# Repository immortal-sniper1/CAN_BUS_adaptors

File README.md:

# CAN_BUS_adaptors
 A few boards that bridge CAN bus to SPI/serial.
 The shields are compatible with:     
  Arduino UNO (or compatible form factor)        
    ESP32 devkitC        
    STM32 NUCLEO-64/144 boards.

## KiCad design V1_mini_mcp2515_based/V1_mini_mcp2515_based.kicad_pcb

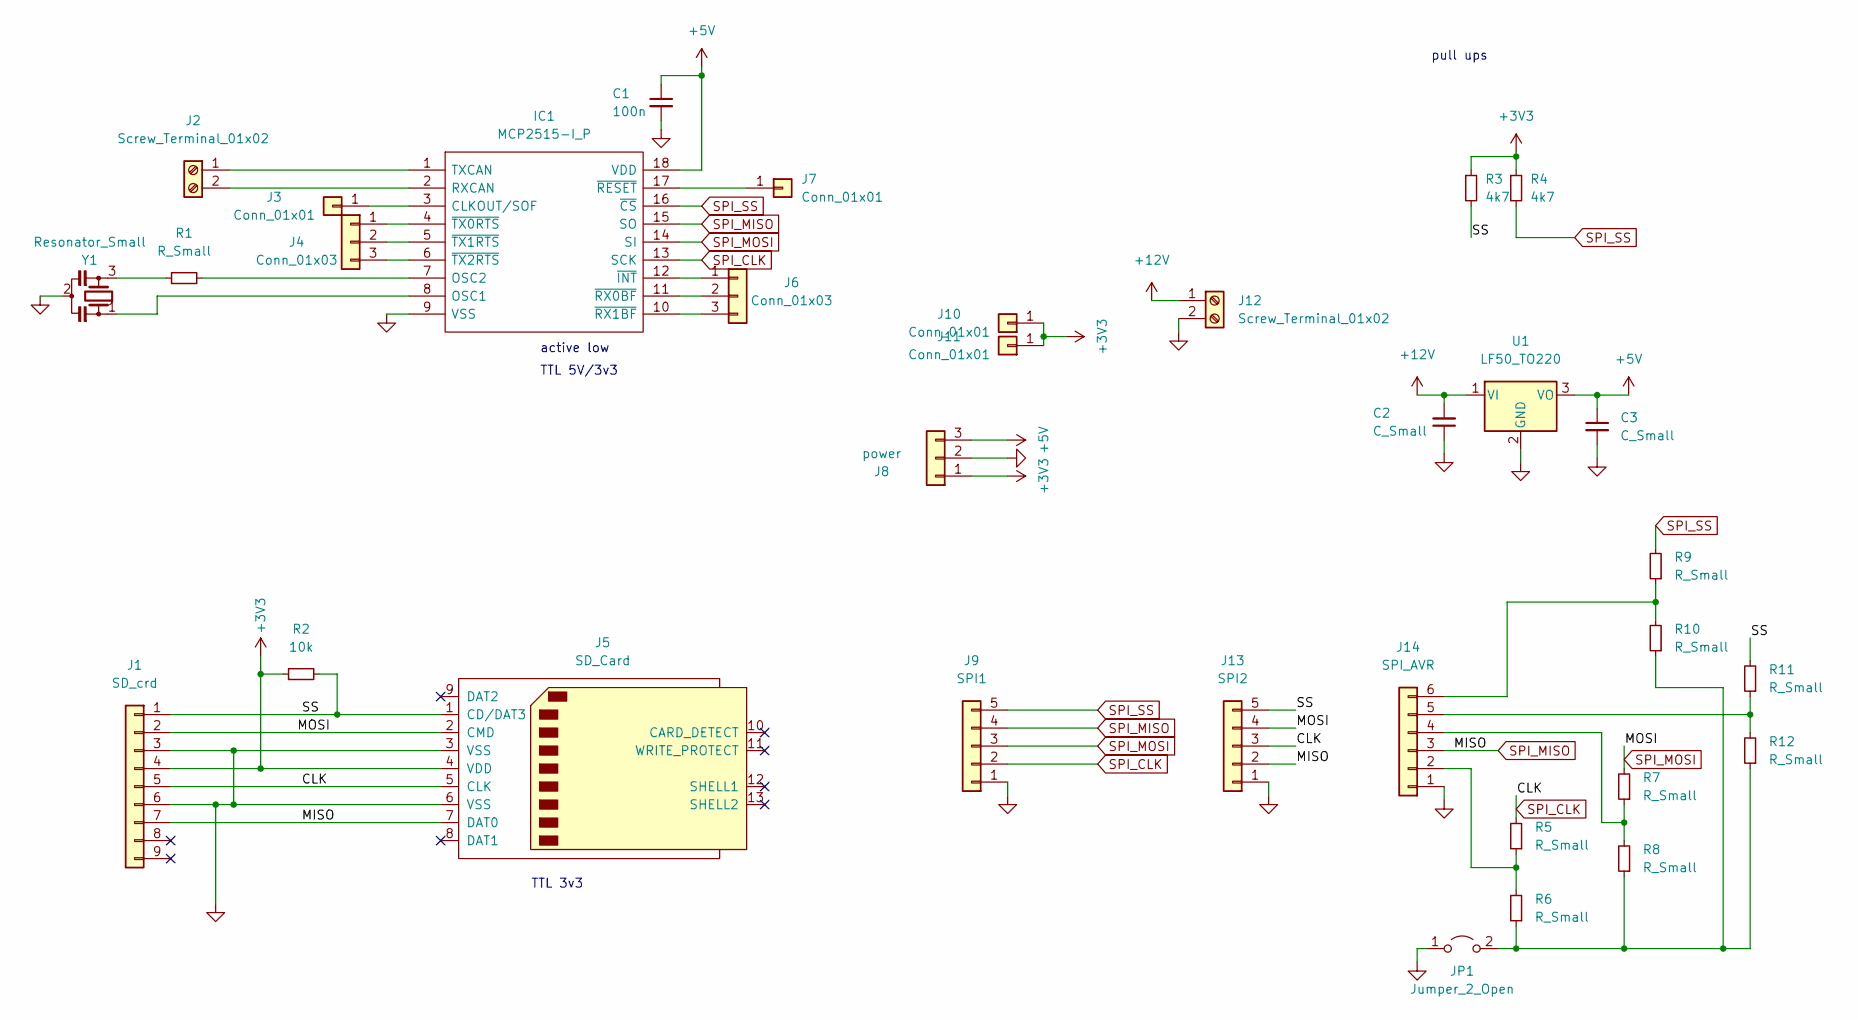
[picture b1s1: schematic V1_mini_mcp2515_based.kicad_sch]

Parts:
C1: 100n; C_Disc_D4.7mm_W2.5mm_P5.00mm
C2, C3: C_Small; C_Disc_D4.3mm_W1.9mm_P5.00mm
IC1: MCP2515-I_P; DIP-18_W7.62mm_LongPads; Mouser Part Number 579-MCP2515-I/P
J1: SD_crd; PinHeader_1x07_P2.54mm_Vertical
J2, J12: Screw_Terminal_01x02; TerminalBlock_Altech_AK300-2_P5.00mm
J3, J7, J10, J11: Conn_01x01; PinHeader_1x01_P2.54mm_Vertical
J4, J6: Conn_01x03; PinHeader_1x03_P2.54mm_Vertical
J5: SD_Card
J8: power; PinHeader_1x03_P2.54mm_Vertical
J9: SPI1; PinHeader_1x05_P2.54mm_Vertical
J13: SPI2; PinHeader_1x05_P2.54mm_Vertical
J14: SPI_AVR; PinHeader_1x06_P2.54mm_Vertical
JP1: Jumper_2_Open; PinHeader_1x02_P2.54mm_Vertical
R1, R5, R6, R7, R8, R9, R10, R11, R12: R_Small; R_Axial_DIN0204_L3.6mm_D1.6mm_P5.08mm_Horizontal
R2: 10k; R_Axial_DIN0204_L3.6mm_D1.6mm_P5.08mm_Horizontal
R3, R4: 4k7; R_Axial_DIN0204_L3.6mm_D1.6mm_P5.08mm_Horizontal
U1: LF50_TO220; TO-220-3_Horizontal_TabDown
Y1: Resonator_Small; Resonator_Murata_CSTLSxxxG-3Pin_W8.0mm_H3.0mm

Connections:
+3V3: J1.4, J5.4 (VDD), J8.1, J10.1, J11.1, R2.1, R3.1, R4.1
+5V: C1.1, C3.1, IC1.18 (VDD), J8.3, U1.3 (VO)
+12V: C2.2, J12.1, U1.1 (VI)
/SS: J1.1, J5.1 (CD/DAT3), J13.5, R2.2, R3.2, R11.2
GND: C1.2, C2.1, C3.2, IC1.9 (VSS), J1.3, J1.6, J5.3 (VSS), J5.6 (VSS), J8.2, J9.1, J12.2, J13.1, J14.1, JP1.1 (A), U1.2 (GND), Y1.2
unnamed: IC1.1 (TXCAN), J2.1
unnamed: IC1.2 (RXCAN), J2.2
unnamed: IC1.3 (CLKOUT/SOF), J3.1
unnamed: IC1.4 (~TX0RTS), J4.1
unnamed: IC1.5 (~TX1RTS), J4.2
unnamed: IC1.6 (~TX2RTS), J4.3
unnamed: IC1.7 (OSC2), R1.2
unnamed: IC1.8 (OSC1), Y1.1
unnamed: IC1.10 (~RX1BF), J6.3
unnamed: IC1.11 (~RX0BF), J6.2
unnamed: IC1.12 (~INT), J6.1
unnamed: IC1.17 (~RESET), J7.1
unnamed: J14.2, R5.1, R6.2
unnamed: J14.4, R7.1, R8.2
unnamed: J14.5, R11.1, R12.2
unnamed: J14.6, R9.1, R10.2
unnamed: JP1.2 (B), R6.1, R8.1, R10.1, R12.1
unnamed: R1.1, Y1.3
SPI_CLK: IC1.13 (SCK), J1.5, J5.5 (CLK), J9.2, J13.3, R5.2
SPI_MISO: IC1.15 (SO), J1.7, J5.7 (DAT0), J9.4, J13.2, J14.3
SPI_MOSI: IC1.14 (SI), J1.2, J5.2 (CMD), J9.3, J13.4, R7.2
SPI_SS: IC1.16 (~CS), J9.5, R4.2, R9.2

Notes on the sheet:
TTL 5V/3v3
active low
pull ups
TTL 3v3

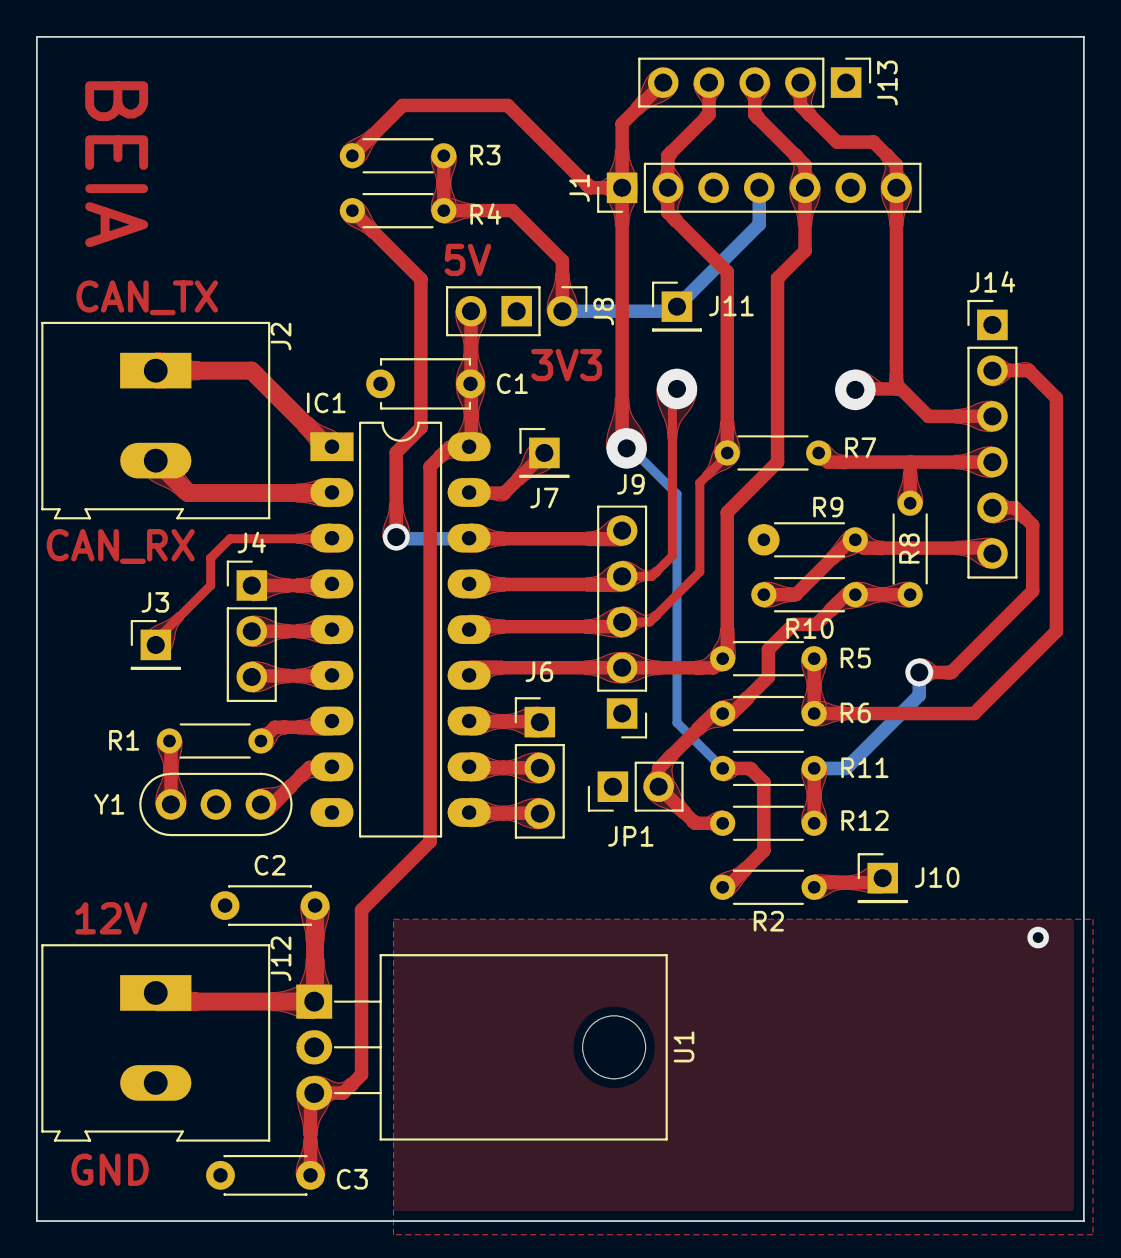
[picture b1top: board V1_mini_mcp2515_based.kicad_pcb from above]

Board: 2 copper layers, 58.2 x 65.8 mm, 32 parts (0 on the bottom side), 27 nets.

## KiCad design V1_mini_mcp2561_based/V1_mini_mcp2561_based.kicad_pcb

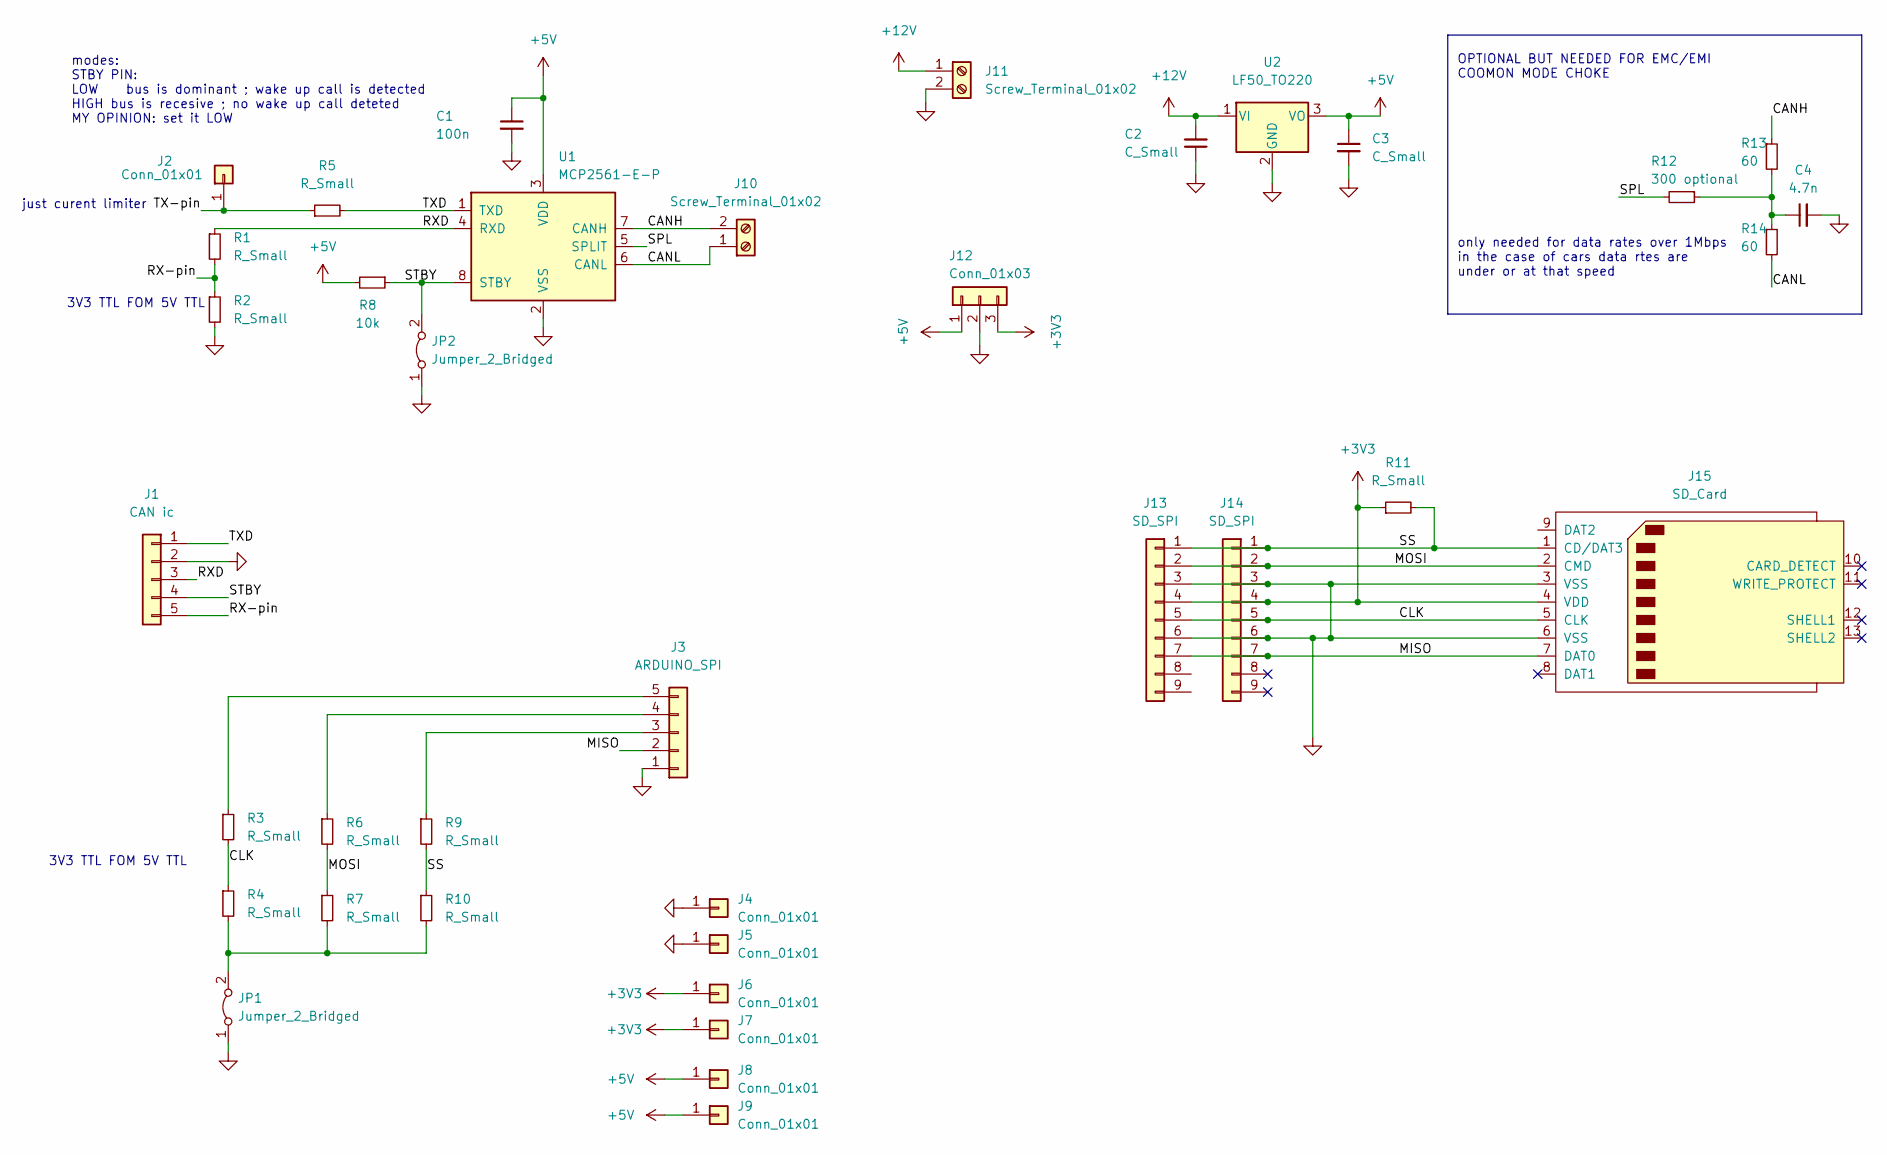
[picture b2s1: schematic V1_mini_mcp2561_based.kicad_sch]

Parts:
C1: 100n; C_Disc_D4.3mm_W1.9mm_P5.00mm
C2: C_Small; CP_Radial_Tantal_D5.0mm_P5.00mm
C3: C_Small; C_Disc_D4.3mm_W1.9mm_P5.00mm
C4: 4.7n; C_Disc_D4.3mm_W1.9mm_P5.00mm
J1: CAN ic; PinHeader_1x05_P2.54mm_Vertical
J2, J4, J5, J6, J7, J8, J9: Conn_01x01; PinHeader_1x01_P2.54mm_Vertical
J3: ARDUINO_SPI; PinHeader_1x05_P2.54mm_Vertical
J10, J11: Screw_Terminal_01x02; TerminalBlock_Altech_AK300-2_P5.00mm
J12: Conn_01x03; PinHeader_1x03_P2.54mm_Vertical
J13, J14: SD_SPI; PinHeader_1x07_P2.54mm_Vertical
J15: SD_Card
JP1, JP2: Jumper_2_Bridged; PinHeader_1x02_P2.54mm_Vertical
R1, R2, R3, R4, R5, R6, R7, R9, R10, R11: R_Small; R_Axial_DIN0204_L3.6mm_D1.6mm_P5.08mm_Horizontal
R8: 10k; R_Axial_DIN0204_L3.6mm_D1.6mm_P5.08mm_Horizontal
R12: 300 optional; R_Axial_DIN0204_L3.6mm_D1.6mm_P5.08mm_Horizontal
R13, R14: 60; R_Axial_DIN0204_L3.6mm_D1.6mm_P5.08mm_Horizontal
U1: MCP2561-E-P; DIP-8_W7.62mm_LongPads
U2: LF50_TO220; TO-220-3_Horizontal_TabDown

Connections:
+3V3: J6.1, J7.1, J12.3, J13.4, J14.4, J15.4 (VDD), R11.1
+5V: C1.1, C3.1, J8.1, J9.1, J12.1, R8.2, U1.3 (VDD), U2.3 (VO)
+12V: C2.2, J11.1, U2.1 (VI)
/CANH: J10.2, R13.1, U1.7 (CANH)
/CANL: J10.1, R14.2, U1.6 (CANL)
/CLK: J13.5, J14.5, J15.5 (CLK), R3.2, R4.1
/MISO: J3.2, J13.7, J14.7, J15.7 (DAT0)
/MOSI: J13.2, J14.2, J15.2 (CMD), R6.2, R7.1
/RX-pin: J1.5, R1.2, R2.1
/RXD: J1.3, R1.1, U1.4 (RXD)
/SPL: R12.2, U1.5 (SPLIT)
/SS: J13.1, J14.1, J15.1 (CD/DAT3), R9.2, R10.1, R11.2
/STBY: J1.4, JP2.2 (B), R8.1, U1.8 (STBY)
/TX-pin: J2.1, R5.1
/TXD: J1.1, R5.2, U1.1 (TXD)
GND: C1.2, C2.1, C3.2, C4.2, J1.2, J3.1, J4.1, J5.1, J11.2, J12.2, J13.3, J13.6, J14.3, J14.6, J15.3 (VSS), J15.6 (VSS), JP1.1 (A), JP2.1 (A), R2.2, U1.2 (VSS), U2.2 (GND)
unnamed: C4.1, R12.1, R13.2, R14.1
unnamed: J3.3, R9.1
unnamed: J3.4, R6.1
unnamed: J3.5, R3.1
unnamed: JP1.2 (B), R4.2, R7.2, R10.2

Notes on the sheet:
3V3 TTL FOM 5V TTL
only needed for data rates over 1Mbps in the case of cars data rtes are under or at that speed
OPTIONAL BUT NEEDED FOR EMC/EMI COOMON MODE CHOKE
modes: STBY PIN: LOW bus is dominant ; wake up call is detected HIGH bus is recesive ; no wake up call deteted MY OPINION: set it LOW
just curent limiter

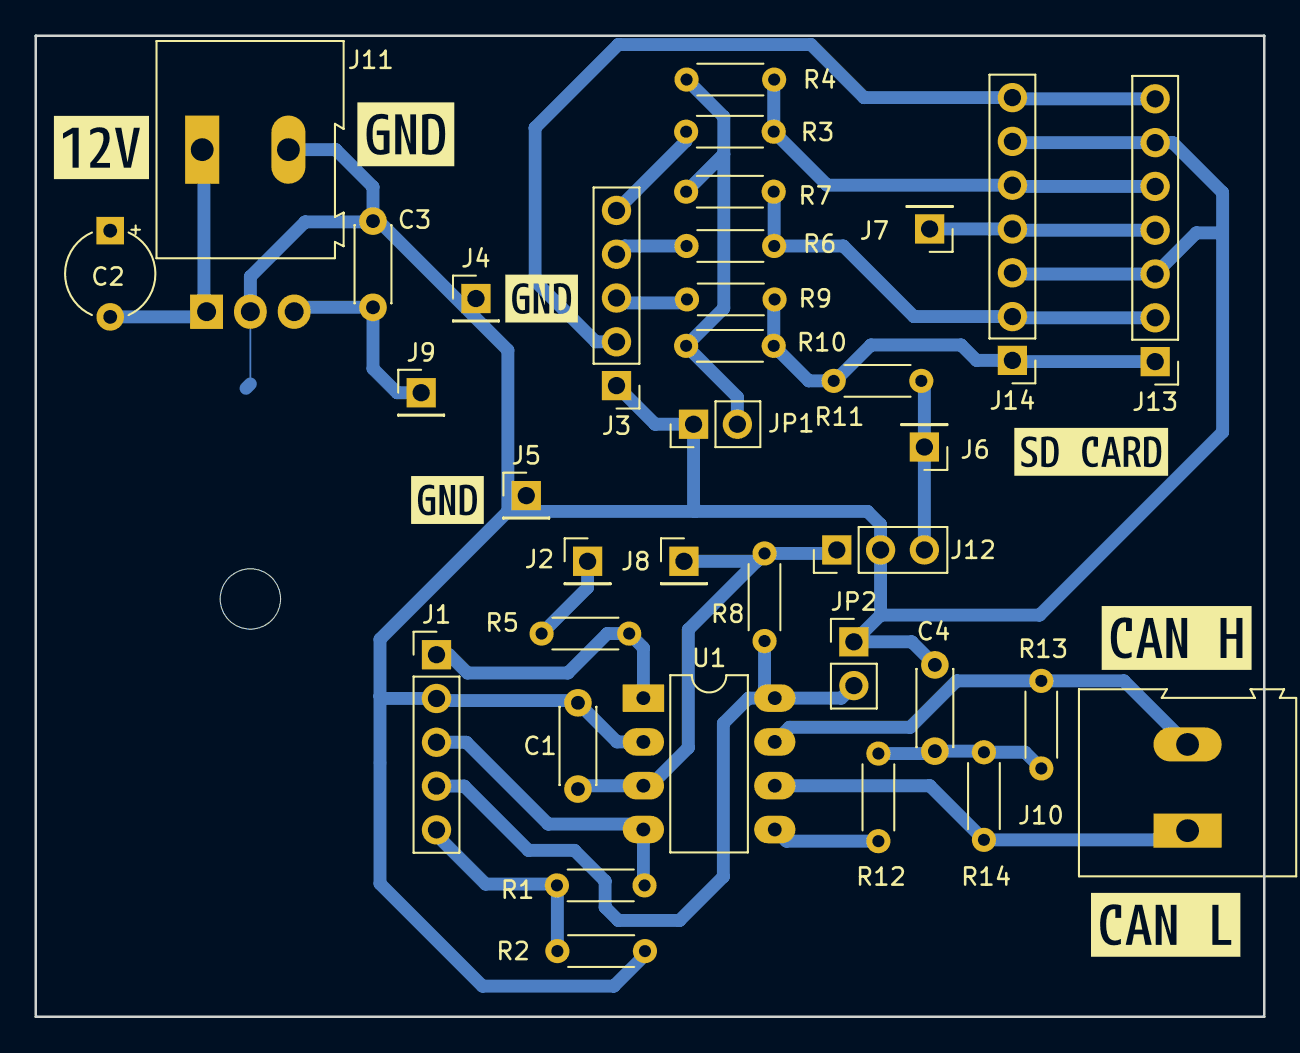
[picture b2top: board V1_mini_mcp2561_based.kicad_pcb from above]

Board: 2 copper layers, 71.2 x 56.9 mm, 43 parts (1 on the bottom side), 21 nets.

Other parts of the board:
kibuzzard-62CE62B6: G***; kibuzzard-62CE62B6
kibuzzard-62CE62BC: G***; kibuzzard-62CE62BC
kibuzzard-62CE62D0: G***; kibuzzard-62CE62D0
kibuzzard-62CE62DA: G***; kibuzzard-62CE62DA
kibuzzard-62CE62ED, kibuzzard-62CE62ED#2: G***; kibuzzard-62CE62ED
kibuzzard-62CE6305: G***; kibuzzard-62CE6305

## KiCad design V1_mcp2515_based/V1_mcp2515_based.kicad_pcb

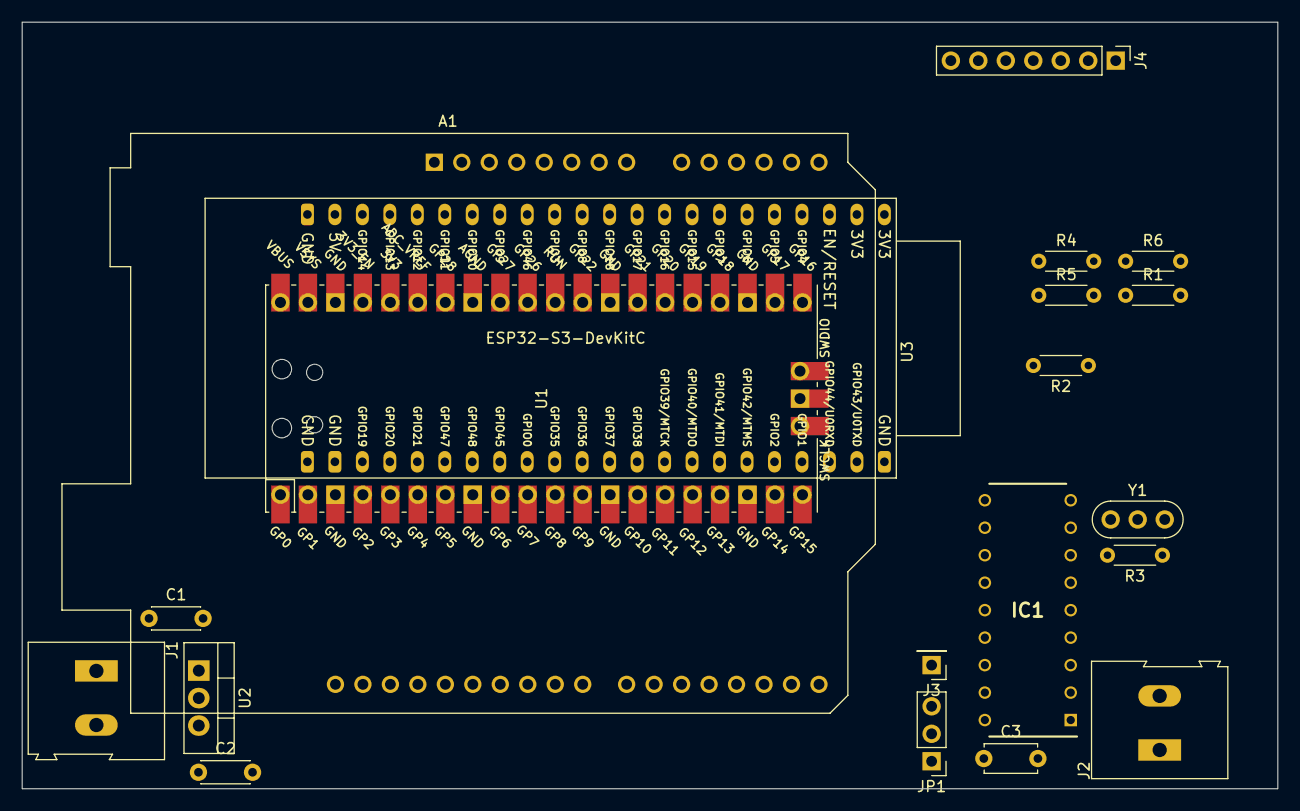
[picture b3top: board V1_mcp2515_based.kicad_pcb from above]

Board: 2 copper layers, 116.1 x 70.9 mm, 20 parts (0 on the bottom side), 17 nets, no tracks yet.

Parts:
A1: Arduino_UNO_R3
C1, C2: C_Small; C_Disc_D4.3mm_W1.9mm_P5.00mm
C3: 100n; C_Disc_D4.7mm_W2.5mm_P5.00mm
IC1: MCP2515-I_P; DIP794W56P254L2286H533Q18N
J1, J2: Screw_Terminal_01x02; TerminalBlock_Altech_AK300-2_P5.00mm
J3: Conn_01x01; PinHeader_1x01_P2.54mm_Vertical
J4: Conn_01x07; PinHeader_1x07_P2.54mm_Vertical
JP1: Jumper_3_Open; PinHeader_1x03_P2.54mm_Vertical
R1, R2: 4k7; R_Axial_DIN0204_L3.6mm_D1.6mm_P5.08mm_Horizontal
R3, R4, R5, R6: R_Small; R_Axial_DIN0204_L3.6mm_D1.6mm_P5.08mm_Horizontal
U1: RP2040; RPi_Pico_SMD_TH
U2: LF50_TO220; TO-220-3_Vertical
U3: ESP32-S3-DevKitC
Y1: Resonator_Small; Resonator_Murata_CSTLSxxxG-3Pin_W8.0mm_H3.0mm

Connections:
+3V3: A1.4 (3V3), J4.4, JP1.3 (B), R1.1, R2.1, R6.1, U1.36 (GPIO24), U3.1 (3V3), U3.2 (3V3)
+5V: A1.5 (+5V), C2.1, JP1.1 (A), U2.3 (VO), U3.21 (5V)
+12V: C1.2, J1.1, U2.1 (VI)
/SS: J4.1, R1.2, R6.2
GND: A1.6 (GND), A1.7 (GND), A1.29 (GND), C1.1, C2.2, C3.2, IC1.9 (VSS), J1.2, J4.3, J4.6, R5.1, U2.2 (GND), U3.22 (GND), U3.23 (GND), U3.24 (GND), U3.44 (GND), Y1.2
unnamed: C3.1, IC1.18 (VDD), JP1.2 (C)
unnamed: IC1.1 (TXCAN), J2.1
unnamed: IC1.2 (RXCAN), J2.2
unnamed: IC1.7 (OSC2), R3.2
unnamed: IC1.8 (OSC1), Y1.1
unnamed: IC1.17 (~RESET), J3.1
unnamed: R3.1, Y1.3
SPI_CLK: A1.13 (SDA/A4), IC1.13 (SCK), U3.20 (GPIO14/ADC2_CH3)
SPI_MISO: A1.12 (A3), IC1.15 (SO), R4.2
SPI_MISO_L: R4.1, R5.2, U3.18 (GPIO12/ADC2_CH1)
SPI_MOSI: A1.11 (A2), IC1.14 (SI), U3.19 (GPIO13/ADC2_CH2)
SPI_SS: A1.10 (A1), IC1.16 (~CS), R2.2, U3.8 (GPIO15/ADC2_CH4/32K_P)

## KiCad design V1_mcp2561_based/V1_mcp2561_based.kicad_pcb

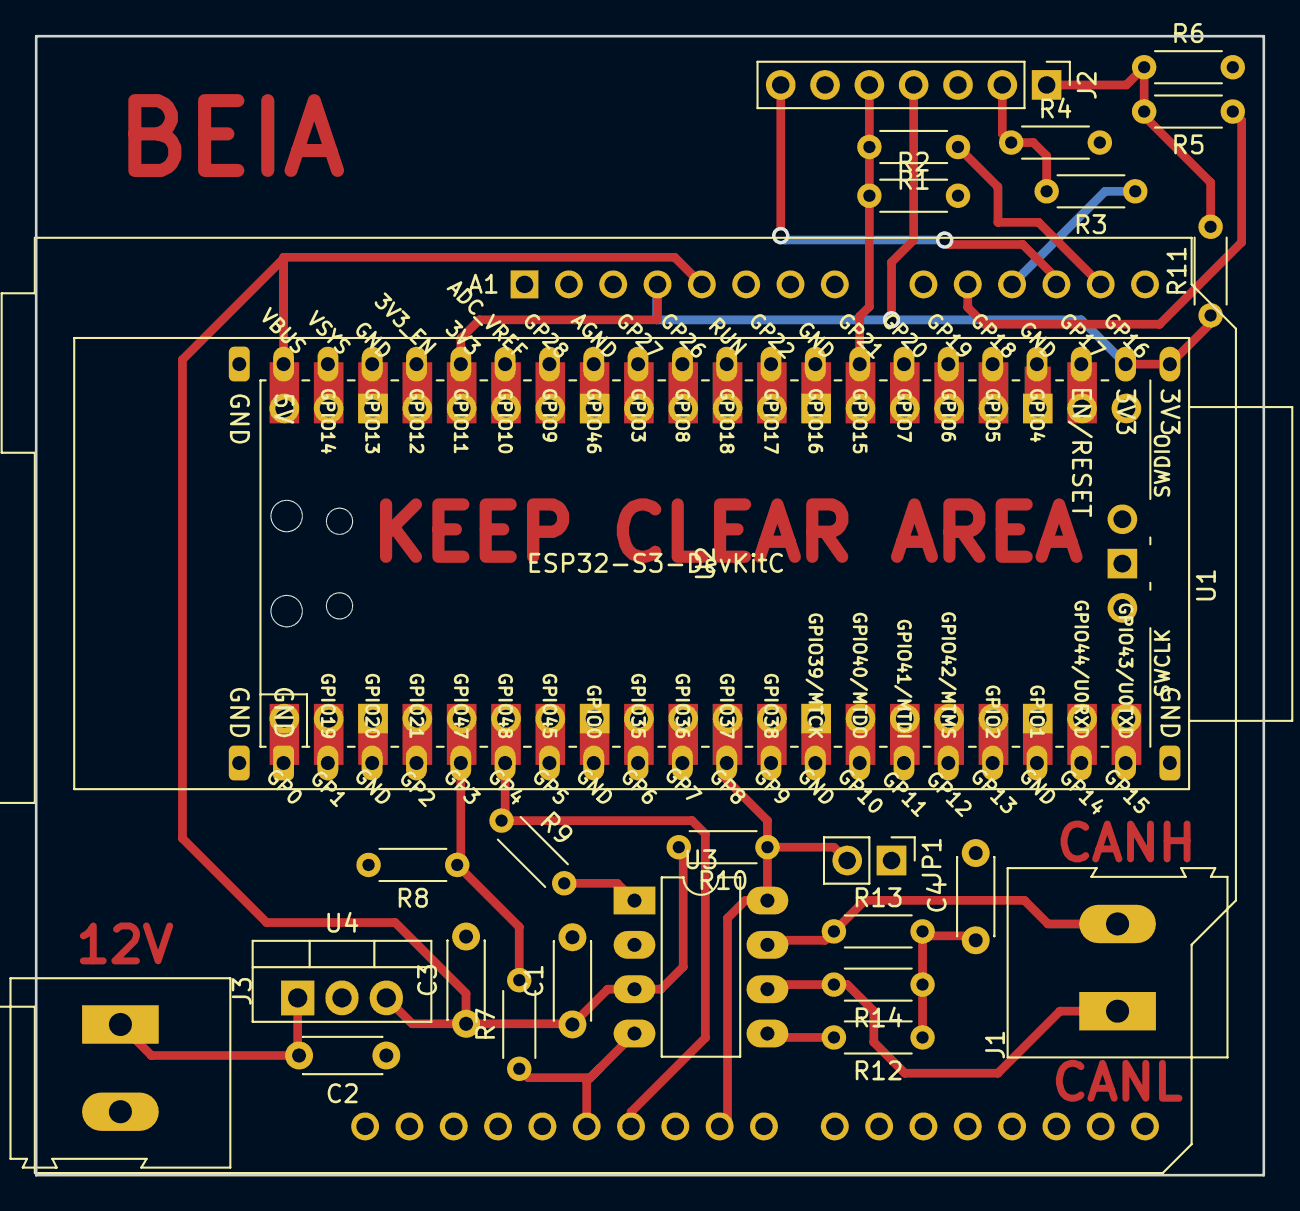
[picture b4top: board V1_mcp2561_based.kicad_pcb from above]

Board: 2 copper layers, 70.4 x 65.3 mm, 27 parts (0 on the bottom side), 20 nets.

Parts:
A1: Arduino_UNO_R3
C1: 100n; C_Disc_D4.3mm_W1.9mm_P5.00mm
C2, C3: C_Small; C_Disc_D4.3mm_W1.9mm_P5.00mm
C4: 4.7n; C_Disc_D4.3mm_W1.9mm_P5.00mm
J1, J3: Screw_Terminal_01x02; TerminalBlock_Altech_AK300-2_P5.00mm
J2: Conn_01x07; PinHeader_1x07_P2.54mm_Vertical
JP1: Jumper_2_Bridged; PinHeader_1x02_P2.54mm_Vertical
R1, R2, R3, R4, R5, R6, R7, R8, R9, R11: R_Small; R_Axial_DIN0204_L3.6mm_D1.6mm_P5.08mm_Horizontal
R10: 10k; R_Axial_DIN0204_L3.6mm_D1.6mm_P5.08mm_Horizontal
R12: 300 optional; R_Axial_DIN0204_L3.6mm_D1.6mm_P5.08mm_Horizontal
R13, R14: 60; R_Axial_DIN0204_L3.6mm_D1.6mm_P5.08mm_Horizontal
U1: ESP32-S3-DevKitC
U2: RP2040; RPi_Pico_SMD_TH
U3: MCP2561-E-P; DIP-8_W7.62mm_LongPads
U4: LF50_TO220; TO-220-3_Vertical

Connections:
+3V3: A1.4 (3V3), J2.4, R11.1, U1.1 (3V3), U1.2 (3V3), U1.17 (GPIO11/ADC2_CH0), U2.36 (GPIO24)
+5V: A1.5 (+5V), C1.1, C3.1, R10.2, U1.21 (5V), U2.40 (GPIO28_ADC2), U3.3 (VDD), U4.3 (VO)
+12V: C2.2, J3.1, U4.1 (VI)
/CANH: J1.2, R13.1, U3.7 (CANH)
/CANL: J1.1, R14.2, U3.6 (CANL)
/CLK: J2.5, R1.2, R2.1, U1.8 (GPIO15/ADC2_CH4/32K_P)
/MISO: A1.12 (A3), J2.7, U1.4 (GPIO4/ADC1_CH3)
/MOSI: J2.2, R3.2, R4.1, U1.6 (GPIO6/ADC1_CH5)
/RX-pin: R7.2, R8.1, U1.28 (GPIO47), U2.5 (GPIO3)
/RXD: A1.27 (D12), R7.1, U3.4 (RXD)
/SPL: R12.2, U3.5 (SPLIT)
/SS: J2.1, R5.2, R6.1, R11.2, U1.5 (GPIO5/ADC1_CH4)
/STBY: A1.24 (D9), JP1.2 (B), R10.1, U1.34 (GPIO37), U2.11 (GPIO8), U3.8 (STBY)
/TX-pin: A1.26 (D11), R9.1, U1.29 (GPIO48), U2.6 (GPIO4)
/TXD: R9.2, U3.1 (TXD)
GND: A1.6 (GND), A1.7 (GND), A1.29 (GND), C1.2, C2.1, C3.2, C4.2, J2.3, J2.6, J3.2, JP1.1 (A), R2.2, R4.2, R6.2, R8.2, U1.22 (GND), U1.23 (GND), U1.24 (GND), U1.44 (GND), U2.1 (IOVDD), U3.2 (VSS), U4.2 (GND)
unnamed: A1.10 (A1), R5.1
unnamed: A1.11 (A2), R3.1
unnamed: A1.13 (SDA/A4), R1.1
unnamed: C4.1, R12.1, R13.2, R14.1
